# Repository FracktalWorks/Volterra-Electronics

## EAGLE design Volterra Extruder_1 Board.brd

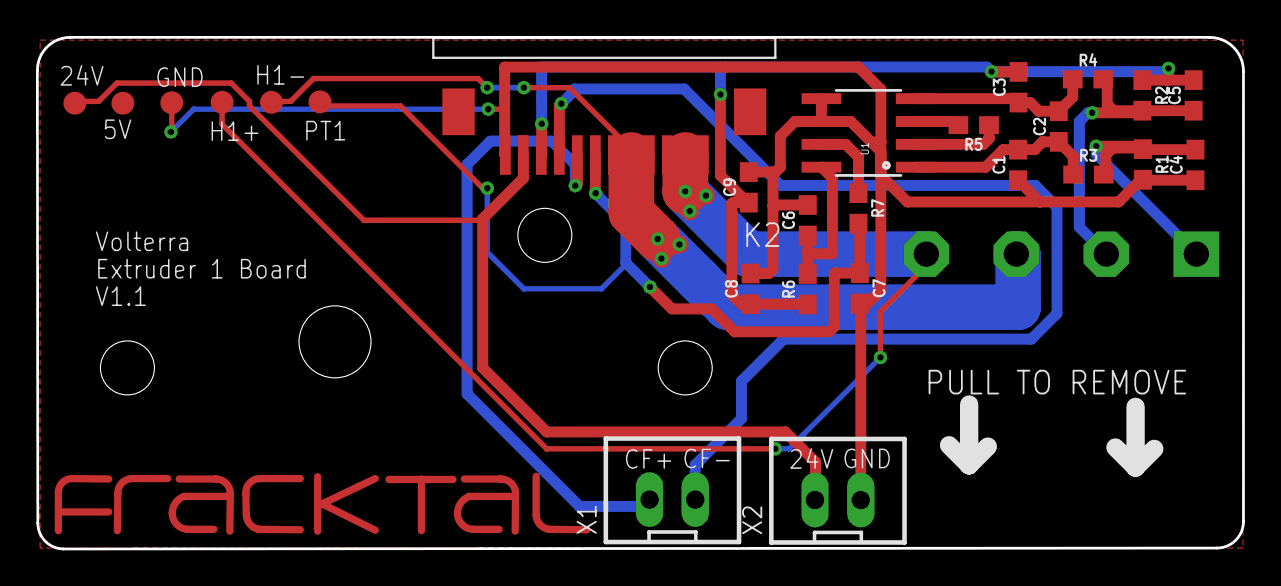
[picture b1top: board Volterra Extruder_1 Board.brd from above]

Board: 2 copper layers, 67.0 x 28.4 mm, 28 parts (1 on the bottom side), 16 nets.

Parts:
C1, C3, C4, C5, C6: 100nF; 0603
C2: 1uF; 0603
C7: 10nF; 0603
C8, C9: 10uF; 0603
J1: TERMINALBLOCK/4PIN/5MMPITCH; TERMINALBLOCK/TOYO/4PIN/5MMPITCH
K2: 68611214122
R1, R2: 2.2k; 0603
R3, R4: 10k; 0603
R5: 5.49k; 0603
R6, R7: 100R; 0603
TP1, TP2, TP6, TP7, TP8, TP9: TEST-POINT3X5; PAD.03X.05
U1: INA826SOIC-08; SOIC-8
U$1: FRACKTALLOGO
X1: CF; JST-XH-02-PACKAGE-LONG-PAD
X2: AOF; JST-XH-02-PACKAGE-LONG-PAD

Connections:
3V3: C3.2, C5.2, C8.1, C9.1, K2.10, R2.1, R6.1
24V: K2.11, TP6.P$1, X2.1
CF+: K2.8, X1.1
CF-: K2.9, X1.2
GND: C1.1, C4.1, C6.2, C7.2, C8.2, C9.2, K2.12, R1.2, TP7.P$1, U1.5, U1.6, X2.2
H1+: J1.4, K2.1, K2.2, K2.3, TP1.P$1
H1-: J1.3, K2.4, K2.5, K2.6, TP2.P$1
IN+: C5.1, J1.2, R2.2, R4.2
IN-: C4.2, J1.1, R1.1, R3.2
unnamed: R5.1, U1.2
unnamed: R5.2, U1.3
unnamed: C1.2, C2.1, R3.1, U1.1
unnamed: C2.2, C3.1, R4.1, U1.4
unnamed: C6.1, R6.2, U1.8
unnamed: R7.1, U1.7
PT1: C7.1, K2.7, R7.2, TP8.P$1

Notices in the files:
parts and their libraries:
Wurth_Elektronik_Electromechanic_FPC_Con: Copyright: Würth Elektronik
SparkFun-Connectors: Licensing: Creative Commons ShareAlike 4.0 International - https://creativecommons.org/licenses/by-sa/4.0
